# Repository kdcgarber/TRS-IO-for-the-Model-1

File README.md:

# TRS-IO model 1

This repo is based on a snapshot of https://github.com/apuder/TRS-IO commit f2acde6.<br>
That repo is an amazing piece of hardware/software that provides new feature to my retro TRS-80 model 1<br>

<table>
  <tr>
    <td>
      <ul>
        <li>Network connection / internet - TCP</li>
        <li>Retrostore</li>
        <li>SMB share</li>
        <li>SD card</li>
        <li>FreHD emulation auto-boot on my unmodified M1</li>
        <li>Upper 32k of memory</li>
        <li>Virtual printer</li>
        <li>HDMI color video / audio out</li>
        <li>Realtime clock</li>
      </ul>
    </td>
    <td>
      
    </td>
  </tr>
</table>

These are just notes for my path to get the v1.4 hardware build configured with the backported TRS-IO++ software that is all found on their site.<br>
Their site is the safe source and is what should be used; mine is just my notes and everything that worked for me.
These are my notes to help me build another in the future and could possibly help someone else as well.<br>
<br>

These are not notes on the pcb build, just the code deploy process for the TRS-IO v1.4.<br>

## Notes

I used the ESP-WROOM-32 esp controller (no PSRAM) - https://www.amazon.com/dp/B0B764963C<br>
And I used the Tang Nano 9K FPGA - https://www.aliexpress.us/item/3256804089255675.html<br>

I did this install/build/deploy on my OrangePi-Zero-2w running Ubuntu 24.04, as a non-root account<br>

### Prep - installing required components<br>
&nbsp;&nbsp;&nbsp;&nbsp;sudo apt upgrade<br>
### Packages for Espressif<br>
&nbsp;&nbsp;&nbsp;&nbsp;sudo apt-get install git wget flex bison gperf python3 python3-pip python3-setuptools cmake ninja-build ccache libffi-dev libssl-dev dfu-util libusb-1.0-0 python3-virtualenv<br>
###  Packages for TRS-IO<br>
&nbsp;&nbsp;&nbsp;&nbsp;sudo apt-get install z80asm sdcc sdcc-libraries<br>
###  Some fixes for linking libraries that are needed by TRS-IO<br>
&nbsp;&nbsp;&nbsp;&nbsp;sudo mkdir -p /lib/z80/<br>
&nbsp;&nbsp;&nbsp;&nbsp;sudo ln -s /usr/share/sdcc/lib/z80/z80.lib /lib/z80/z80.lib<br>
###  Python3 as default:<br>
&nbsp;&nbsp;&nbsp;&nbsp;sudo apt-get install python3 python3-pip python3-setuptools<br>
&nbsp;&nbsp;&nbsp;&nbsp;sudo ln -s /usr/bin/python3 /usr/bin/python<br>
<br>

###  Install ESP-IDF<br>
cd ~/<br>
mkdir esp<br>
cd esp<br>
git clone -b v4.4.7 --recurse-submodules https://github.com/espressif/esp-idf.git<br>
cd ~/esp/esp-idf<br>
./install.sh esp32<br>

### TRS-IO stuff<br>
.  ~/esp/esp-idf/export.sh<br>
cd ~/esp<br>
git clone -b master --recurse-submodules https://github.com/apuder/TRS-IO.git <br>
cd ~/esp/TRS-IO/src/esp/ <br>

### Copy sdkconfig.trs-io-m1 to sdkconfig.trs-io-m1-v14<br>
cp sdkconfig.trs-io-m1 sdkconfig.trs-io-m1-v14<br>
<br>
### Then add to the bottom of the sdkconfig.trs-io-m1-v14<br>
CONFIG_SPIRAM_SUPPORT=n<br>

### Added logging to the event handler   ~/esp/TRS-IO/src/esp/components/trs-io/http.cpp <br>
This is not required, I add additional logging just lets me validate memory available as the event handler is triggered at the time of the showing of web server events.<br>
    ESP_LOGI(TAG, "Free heap: %u", esp_get_free_heap_size());<br>

vim   ~/esp/TRS-IO/src/esp/components/trs-io/http.cpp <br>
It should look like this<br>

	static void mongoose_event_handler(struct mg_connection *c,
					   int event, void *eventData, void *fn_data)
	{
	  static bool reboot = false;

	  // Return if the web debugger is handling the request.
	  if (trx_handle_http_request(c, event, eventData, fn_data)) {
	    return;
	  }

	  switch (event) {
	  case MG_EV_HTTP_MSG:
	    {
	      struct mg_http_message* message = (struct mg_http_message*) eventData;
	      ESP_LOGI(TAG, "request %.*s %.*s",
		      message->method.len,
		      message->method.ptr,
		      message->uri.len,
		      message->uri.ptr);

	      ESP_LOGI(TAG, "Free heap: %u", esp_get_free_heap_size());

	      char* response = NULL; // Always allocated.
	      const char* content_type = "text/html"; // Never allocated

<br>

### Then lowered the max_files value to save memory for the SD card usage.<br>

vim components/trs-fs/posix.cpp<br>
 .max_files = 3,  // 2 works also -- changed from 5<br>

<br>

### Then I changed the LED GPIO values to match the colors for the current v1.4 PCB since mine are RGB, not RBG<br>

This is not needed if you buy LEDs that are RBG, instead of what I bought.<vr>
vim ~/esp/TRS-IO/src/esp/main/led.cpp<br>
#ifdef CONFIG_TRS_IO_MODEL_1<br>
#define LED_RED 5<br>
#define LED_GREEN 4<br>
#define LED_BLUE 32<br>
<br>

# Build<br>
cd ~/esp/TRS-IO/src/esp<br>
idf.py fullclean<br>
make BOARD=trs-io-m1-v14 build<br>

The build will show many  warnings, but if it completes with no errors, the the rest should be good.<br>
At the bottom of its output, it lists the command to run. The port needs to be changed to match the correct port.<br>

Sometimes while doing the flash, it fails. If it does, just try it again and it will load.<br><br>
~/esp/esp-idf/components/esptool_py/esptool/esptool.py -p /dev/ttyUSB0  -b 460800 --before default_reset --after hard_reset --chip esp32  write_flash --flash_mode dio --flash_size detect --flash_freq 40m 0x1000 build/bootloader/bootloader.bin 0x8000 build/partition_table/partition-table.bin 0x10000 build/trs-io.bin 0x190000 build/html.bin<br>

<br><br><br>

# Flash the FPGA

### Install openFPGALoader

apt install \\<br>
  git \\<br>
  gzip \\<br>
  libftdi1-2 \\<br>
  libftdi1-dev \\<br>
  libhidapi-hidraw0 \\<br>
  libhidapi-dev \\<br>
  libudev-dev \\<br>
  zlib1g-dev \\<br>
  cmake \\<br>
  pkg-config \\<br>
  make \\<br>
  g++

git clone https://github.com/trabucayre/openFPGALoader<br>
cd openFPGALoader<br>
mkdir build<br>
cd build<br>
cmake .. <br>
cmake --build .<br>
make install<br>

### The FPGA file is TRS-IO.fs<br>

cd  ~/esp/build<br>
openFPGALoader -b tangnano9k -f TRS-IO.fs

		EXAMPLE:
		root@thebox:/home/kdcgarber/esp/buildFiles# openFPGALoader -b tangnano9k -f TRS-IO.fs
		
		empty
		write to flash
		Jtag frequency : requested 6.00MHz   -> real 6.00MHz
		Parse file Parse TRS-IO.fs:
		Done
		DONE
		Jtag frequency : requested 2.50MHz   -> real 2.00MHz
		Erase SRAM DONE
		Erase FLASH DONE
		Erasing FLASH: [==================================================] 100.00%
		Done
		write Flash: [==================================================] 100.00%
		Done
		CRC check: Success

<br>

## All done with the Install

After the install is complete, follow the notes on the TRS-IO site to bring up the trs-io.local access point and start the configuration.<br>
The site has the ROM boot loader for the FreHD to go on the SD card or the smb (windows share or for me SAMBA share on my Linux server).<br>

<br><br><br><br>

## Other notes

### FPGA LED values
wire esp_status_esp_ready   = esp_status[0];<br>
wire esp_status_wifi_up     = esp_status[1];<br>
wire esp_status_smb_mounted = esp_status[2];<br>
wire esp_status_sd_mounted  = esp_status[3];<br>

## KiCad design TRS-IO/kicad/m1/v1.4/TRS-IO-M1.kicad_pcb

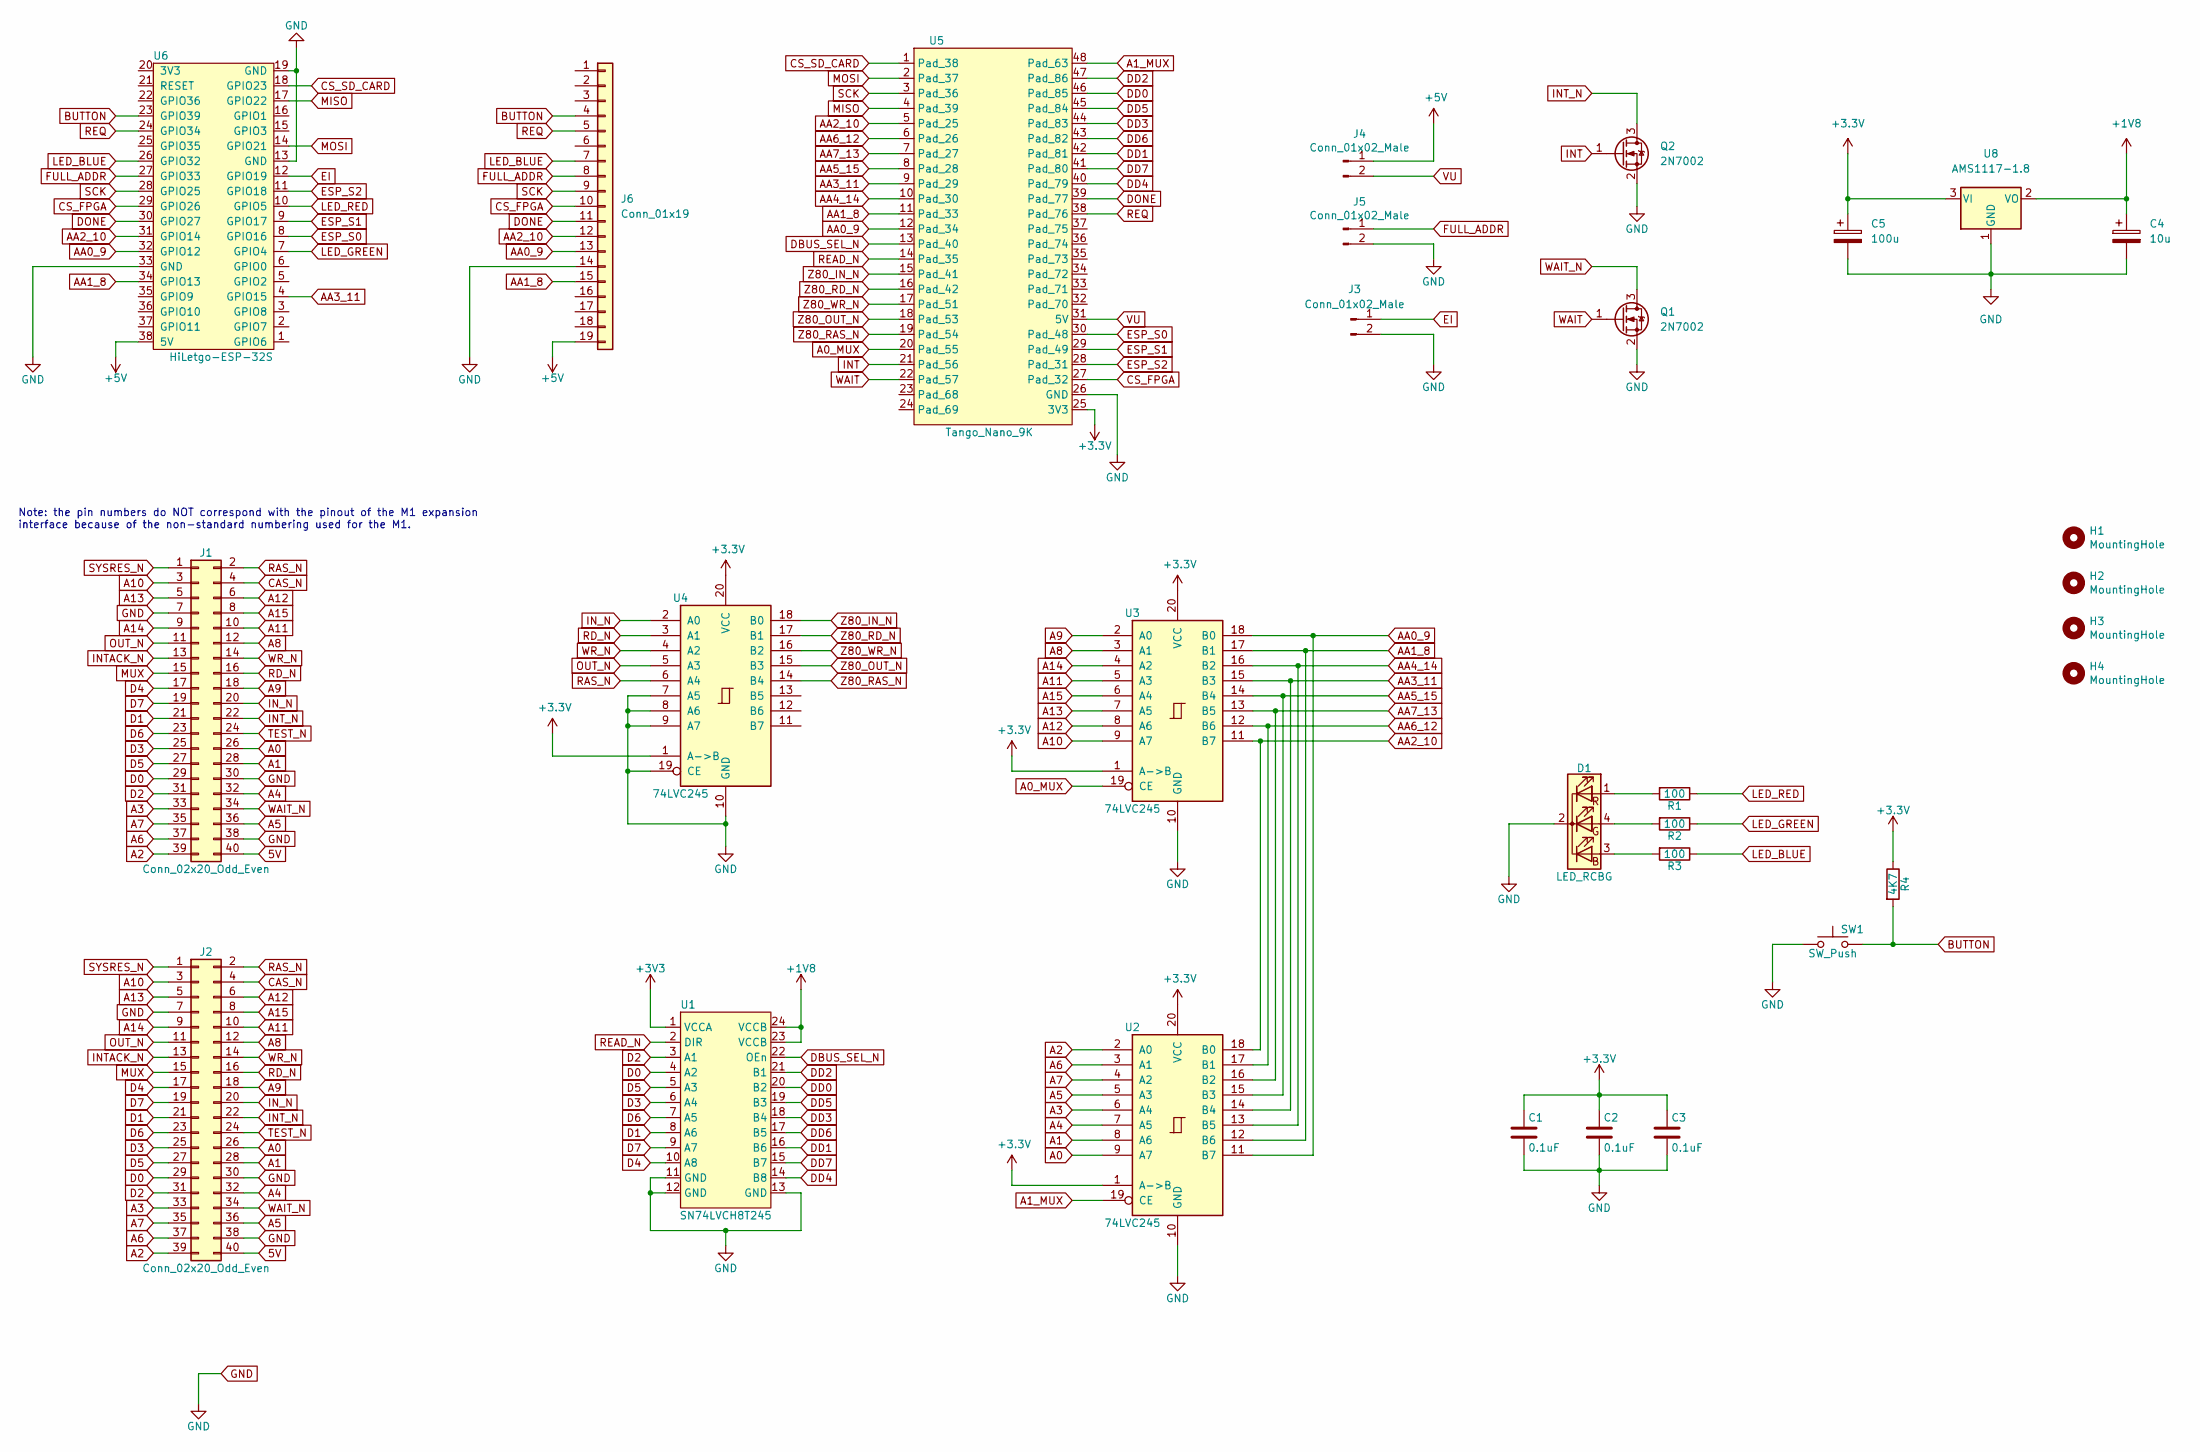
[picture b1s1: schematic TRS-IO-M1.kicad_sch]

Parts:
C1, C2, C3: 0.1uF; C_0805_2012Metric_Pad1.18x1.45mm_HandSolder
C4: 10u; C_1206_3216Metric_Pad1.33x1.80mm_HandSolder
C5: 100u; C_1206_3216Metric_Pad1.33x1.80mm_HandSolder
D1: LED_RCBG; LED_D5.0mm-4_RGB
H1, H2, H3, H4: MountingHole; MountingHole_3mm_Pad_Via
J1: Conn_02x20_Odd_Even; PinHeader_2x20_P2.54mm_Vertical
J2: Conn_02x20_Odd_Even; TRSEDGE
J3, J4, J5: Conn_01x02_Male; PinHeader_1x02_P2.54mm_Vertical
J6: Conn_01x19; PinHeader_1x19_P2.54mm_Vertical
Q1, Q2: 2N7002; SOT-23
R1, R2, R3: 100; R_0805_2012Metric_Pad1.20x1.40mm_HandSolder
R4: 4K7; R_0805_2012Metric_Pad1.20x1.40mm_HandSolder
SW1: SW_Push; SW_PUSH_6mm_H9.5mm
U1: SN74LVCH8T245; TSSOP-24_4.4x7.8mm_P0.65mm
U2, U3, U4: 74LVC245; SSOP-20_5.3x7.2mm_P0.65mm_slim
U5: Tango_Nano_9K; DIP-48_W22.9mm
U6: HiLetgo-ESP-32S; DIP-38_W22.9mm
U8: AMS1117-1.8; SOT-223-3_TabPin2

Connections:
5V: J1.40, J2.40
+1V8: C4.1, U1.23 (VCCB), U1.24 (VCCB), U8.2 (VO)
+5V: J4.1, J6.19, U6.38 (5V)
A0: J1.26, J2.26, U2.9 (A7)
A0_MUX: U3.19 (CE), U5.20 (Pad_55)
A1: J1.28, J2.28, U2.8 (A6)
A1_MUX: U2.19 (CE), U5.48 (Pad_63)
A2: J1.39, J2.39, U2.2 (A0)
A3: J1.33, J2.33, U2.6 (A4)
A4: J1.32, J2.32, U2.7 (A5)
A5: J1.36, J2.36, U2.5 (A3)
A6: J1.37, J2.37, U2.3 (A1)
A7: J1.35, J2.35, U2.4 (A2)
A8: J1.12, J2.12, U3.3 (A1)
A9: J1.18, J2.18, U3.2 (A0)
A10: J1.3, J2.3, U3.9 (A7)
A11: J1.10, J2.10, U3.5 (A3)
A12: J1.6, J2.6, U3.8 (A6)
A13: J1.5, J2.5, U3.7 (A5)
A14: J1.9, J2.9, U3.4 (A2)
A15: J1.8, J2.8, U3.6 (A4)
AA0_9: J6.13, U2.11 (B7), U3.18 (B0), U5.12 (Pad_34), U6.32 (GPIO12)
AA1_8: J6.15, U2.12 (B6), U3.17 (B1), U5.11 (Pad_33), U6.34 (GPIO13)
AA2_10: J6.12, U2.18 (B0), U3.11 (B7), U5.5 (Pad_25), U6.31 (GPIO14)
AA3_11: U2.14 (B4), U3.15 (B3), U5.9 (Pad_29), U6.4 (GPIO15)
AA4_14: U2.13 (B5), U3.16 (B2), U5.10 (Pad_30)
AA5_15: U2.15 (B3), U3.14 (B4), U5.8 (Pad_28)
AA6_12: U2.17 (B1), U3.12 (B6), U5.6 (Pad_26)
AA7_13: U2.16 (B2), U3.13 (B5), U5.7 (Pad_27)
BUTTON: J6.4, R4.2, SW1.2, U6.23 (GPIO39)
CAS_N: J1.4, J2.4
CS_FPGA: J6.10, U5.27 (Pad_32), U6.29 (GPIO26)
CS_SD_CARD: U5.1 (Pad_38), U6.18 (GPIO23)
D0: J1.29, J2.29, U1.4 (A2)
D1: J1.21, J2.21, U1.8 (A6)
D2: J1.31, J2.31, U1.3 (A1)
D3: J1.25, J2.25, U1.6 (A4)
D4: J1.17, J2.17, U1.10 (A8)
D5: J1.27, J2.27, U1.5 (A3)
D6: J1.23, J2.23, U1.7 (A5)
D7: J1.19, J2.19, U1.9 (A7)
DBUS_SEL_N: U1.22 (OEn), U5.13 (Pad_40)
DD0: U1.20 (B2), U5.46 (Pad_85)
DD1: U1.16 (B6), U5.42 (Pad_81)
DD2: U1.21 (B1), U5.47 (Pad_86)
DD3: U1.18 (B4), U5.44 (Pad_83)
DD4: U1.14 (B8), U5.40 (Pad_79)
DD5: U1.19 (B3), U5.45 (Pad_84)
DD6: U1.17 (B5), U5.43 (Pad_82)
DD7: U1.15 (B7), U5.41 (Pad_80)
DONE: J6.11, U5.39 (Pad_77), U6.30 (GPIO27)
EI: J3.1, U6.12 (GPIO19)
ESP_S0: U5.30 (Pad_48), U6.8 (GPIO16)
ESP_S1: U5.29 (Pad_49), U6.9 (GPIO17)
ESP_S2: U5.28 (Pad_31), U6.11 (GPIO18)
FULL_ADDR: J5.1, J6.8, U6.27 (GPIO33)
GND: C1.2, C2.2, C3.2, C4.2, C5.2, D1.2 (K), J1.7, J1.30, J1.38, J2.7, J2.30, J2.38, J3.2, J5.2, J6.14, Q1.2 (S), Q2.2 (S), SW1.1, U1.11 (GND), U1.12 (GND), U1.13 (GND), U2.10 (GND), U3.10 (GND), U4.7 (A5), U4.8 (A6), U4.9 (A7), U4.10 (GND), U4.19 (CE), U5.26 (GND), U6.13 (GND), U6.19 (GND), U6.33 (GND), U8.1 (GND)
INT: Q2.1 (G), U5.21 (Pad_56)
INTACK_N: J1.13, J2.13
INT_N: J1.22, J2.22, Q2.3 (D)
IN_N: J1.20, J2.20, U4.2 (A0)
LED_BLUE: J6.7, R3.1, U6.26 (GPIO32)
LED_GREEN: R2.1, U6.7 (GPIO4)
LED_RED: R1.1, U6.10 (GPIO5)
MISO: U5.4 (Pad_39), U6.17 (GPIO22)
MOSI: U5.2 (Pad_37), U6.14 (GPIO21)
MUX: J1.15, J2.15
unnamed: D1.1 (RA), R1.2
unnamed: D1.3 (BA), R3.2
unnamed: D1.4 (GA), R2.2
OUT_N: J1.11, J2.11, U4.5 (A3)
RAS_N: J1.2, J2.2, U4.6 (A4)
RD_N: J1.16, J2.16, U4.3 (A1)
READ_N: U1.2 (DIR), U5.14 (Pad_35)
REQ: J6.5, U5.38 (Pad_76), U6.24 (GPIO34)
SCK: J6.9, U5.3 (Pad_36), U6.28 (GPIO25)
SYSRES_N: J1.1, J2.1
TEST_N: J1.24, J2.24
VU: J4.2, U5.31 (5V)
WAIT: Q1.1 (G), U5.22 (Pad_57)
WAIT_N: J1.34, J2.34, Q1.3 (D)
WR_N: J1.14, J2.14, U4.4 (A2)
Z80_IN_N: U4.18 (B0), U5.15 (Pad_41)
Z80_OUT_N: U4.15 (B3), U5.18 (Pad_53)
Z80_RAS_N: U4.14 (B4), U5.19 (Pad_54)
Z80_RD_N: U4.17 (B1), U5.16 (Pad_42)
Z80_WR_N: U4.16 (B2), U5.17 (Pad_51)

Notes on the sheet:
Note: the pin numbers do NOT correspond with the pinout of the M1 expansion interface because of the non-standard numbering used for the M1.

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
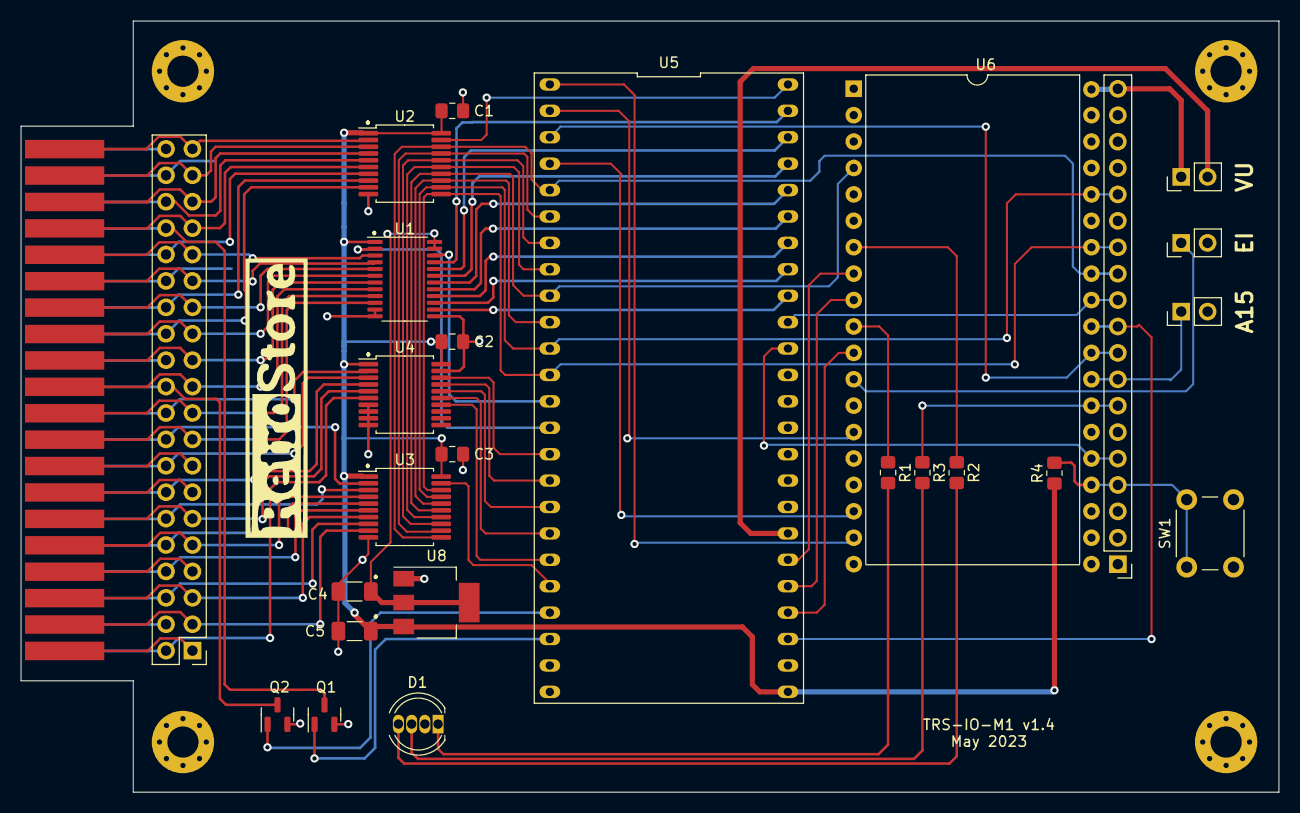
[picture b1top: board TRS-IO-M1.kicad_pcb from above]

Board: 2 copper layers, 121.0 x 74.2 mm, 31 parts (0 on the bottom side), 88 nets.

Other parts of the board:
G1: LOGO

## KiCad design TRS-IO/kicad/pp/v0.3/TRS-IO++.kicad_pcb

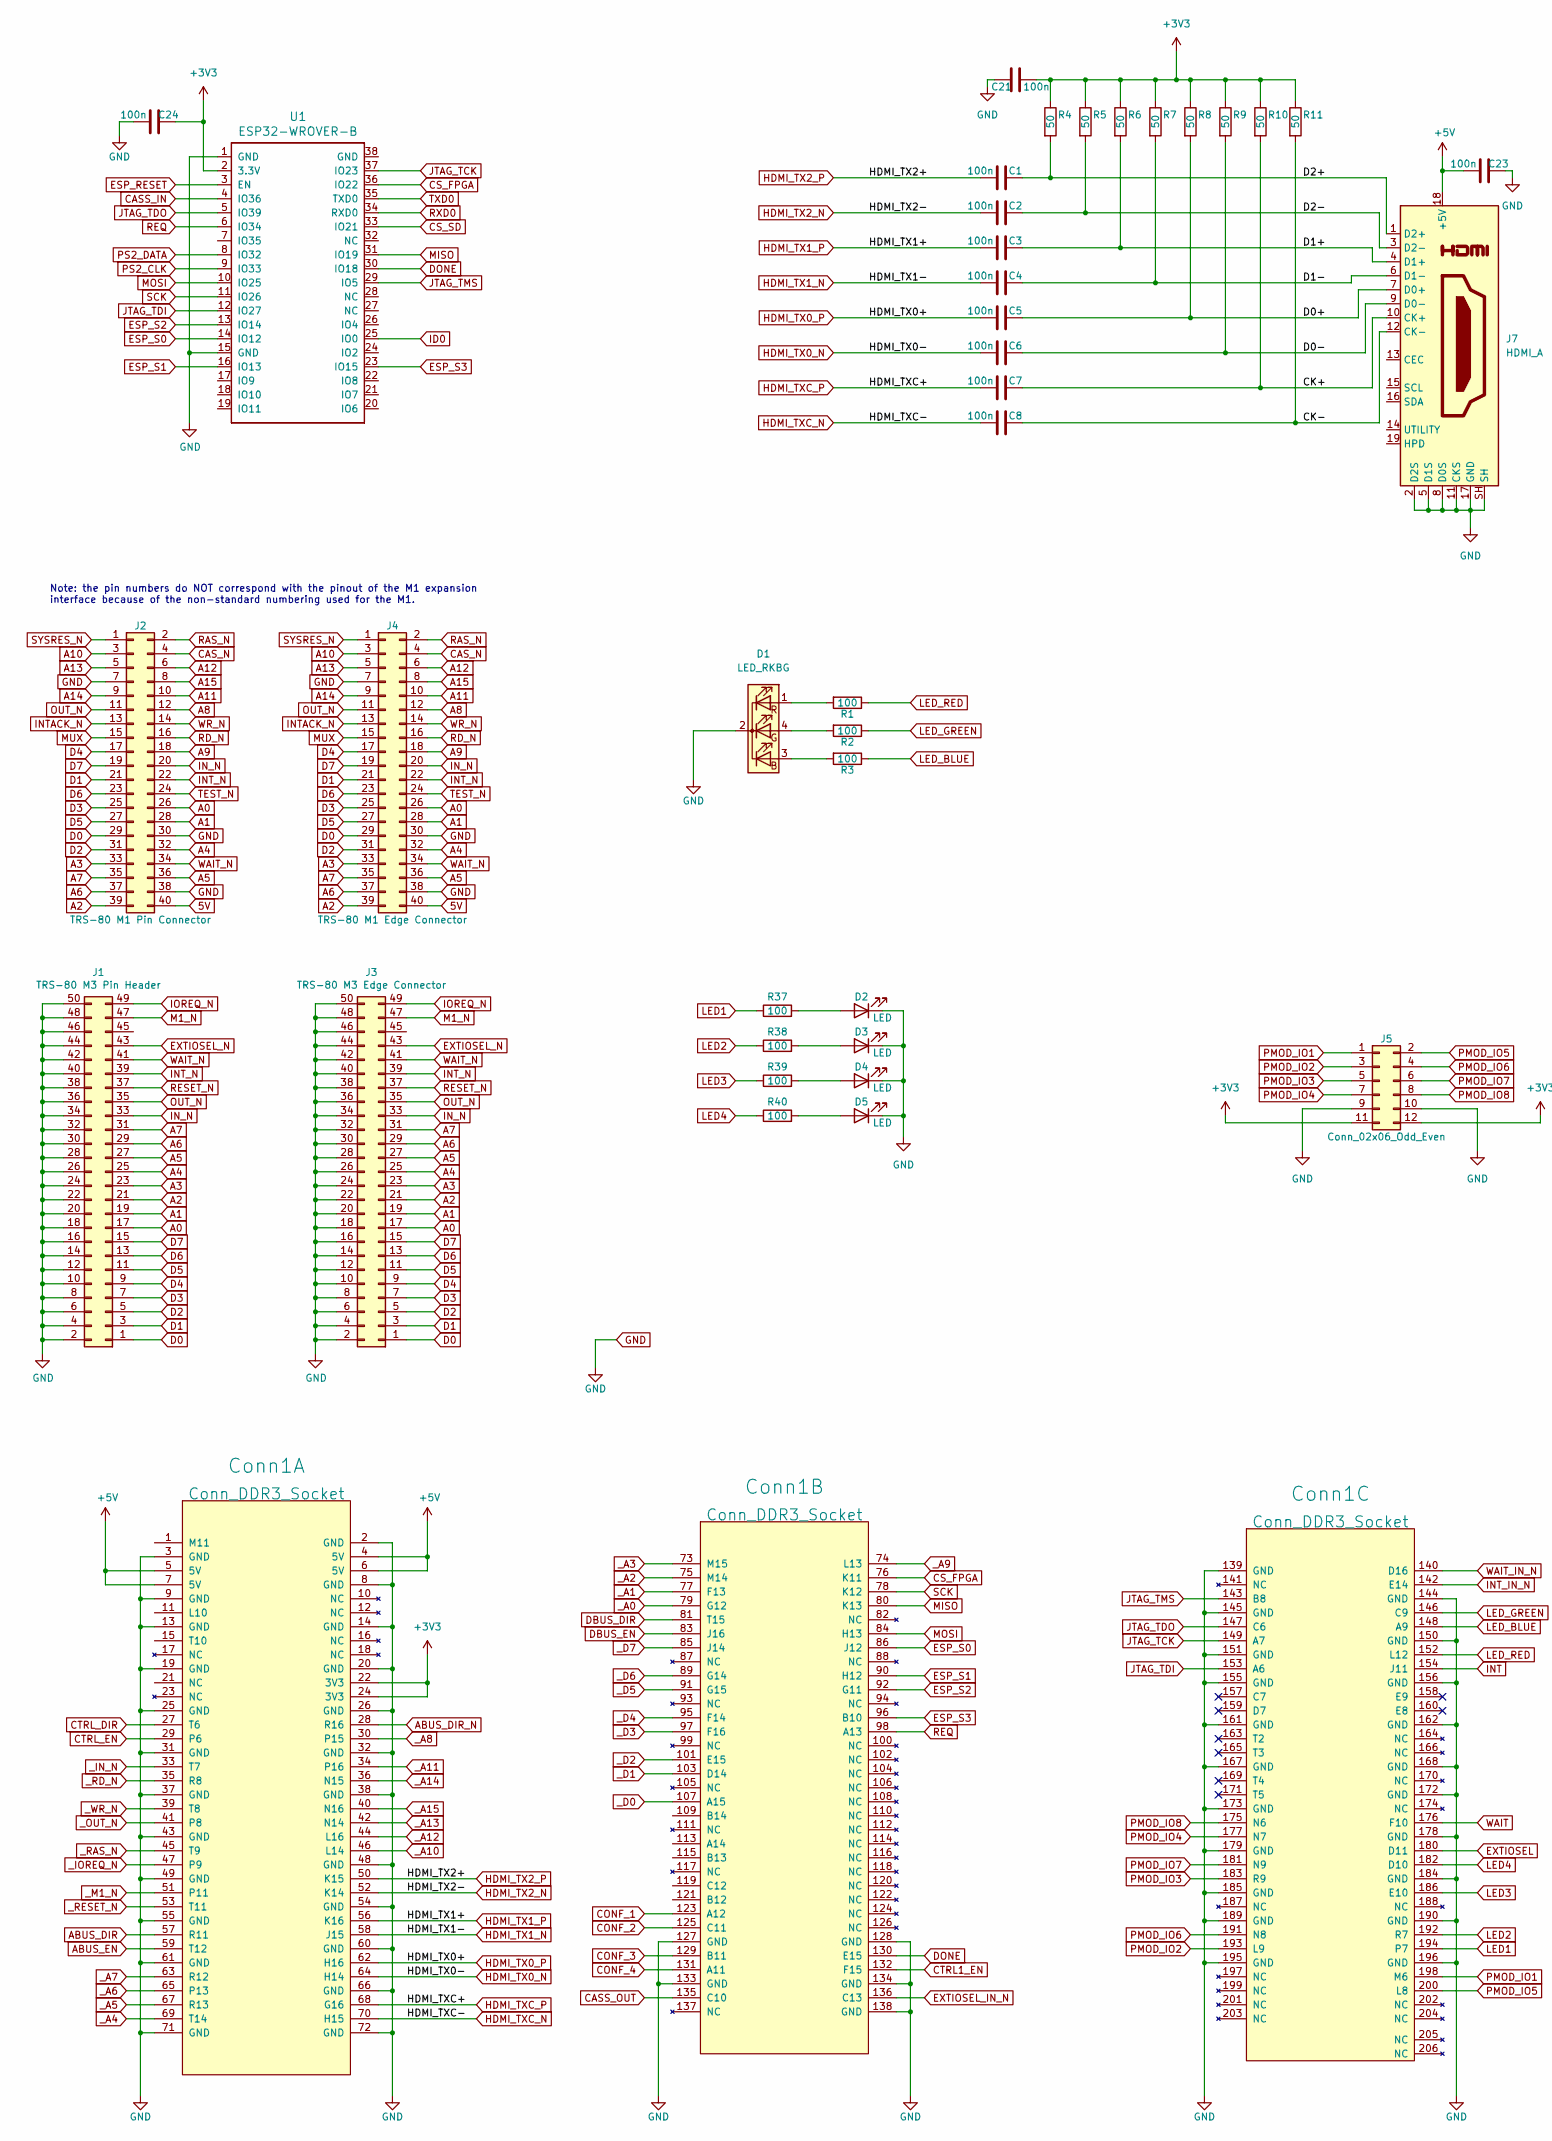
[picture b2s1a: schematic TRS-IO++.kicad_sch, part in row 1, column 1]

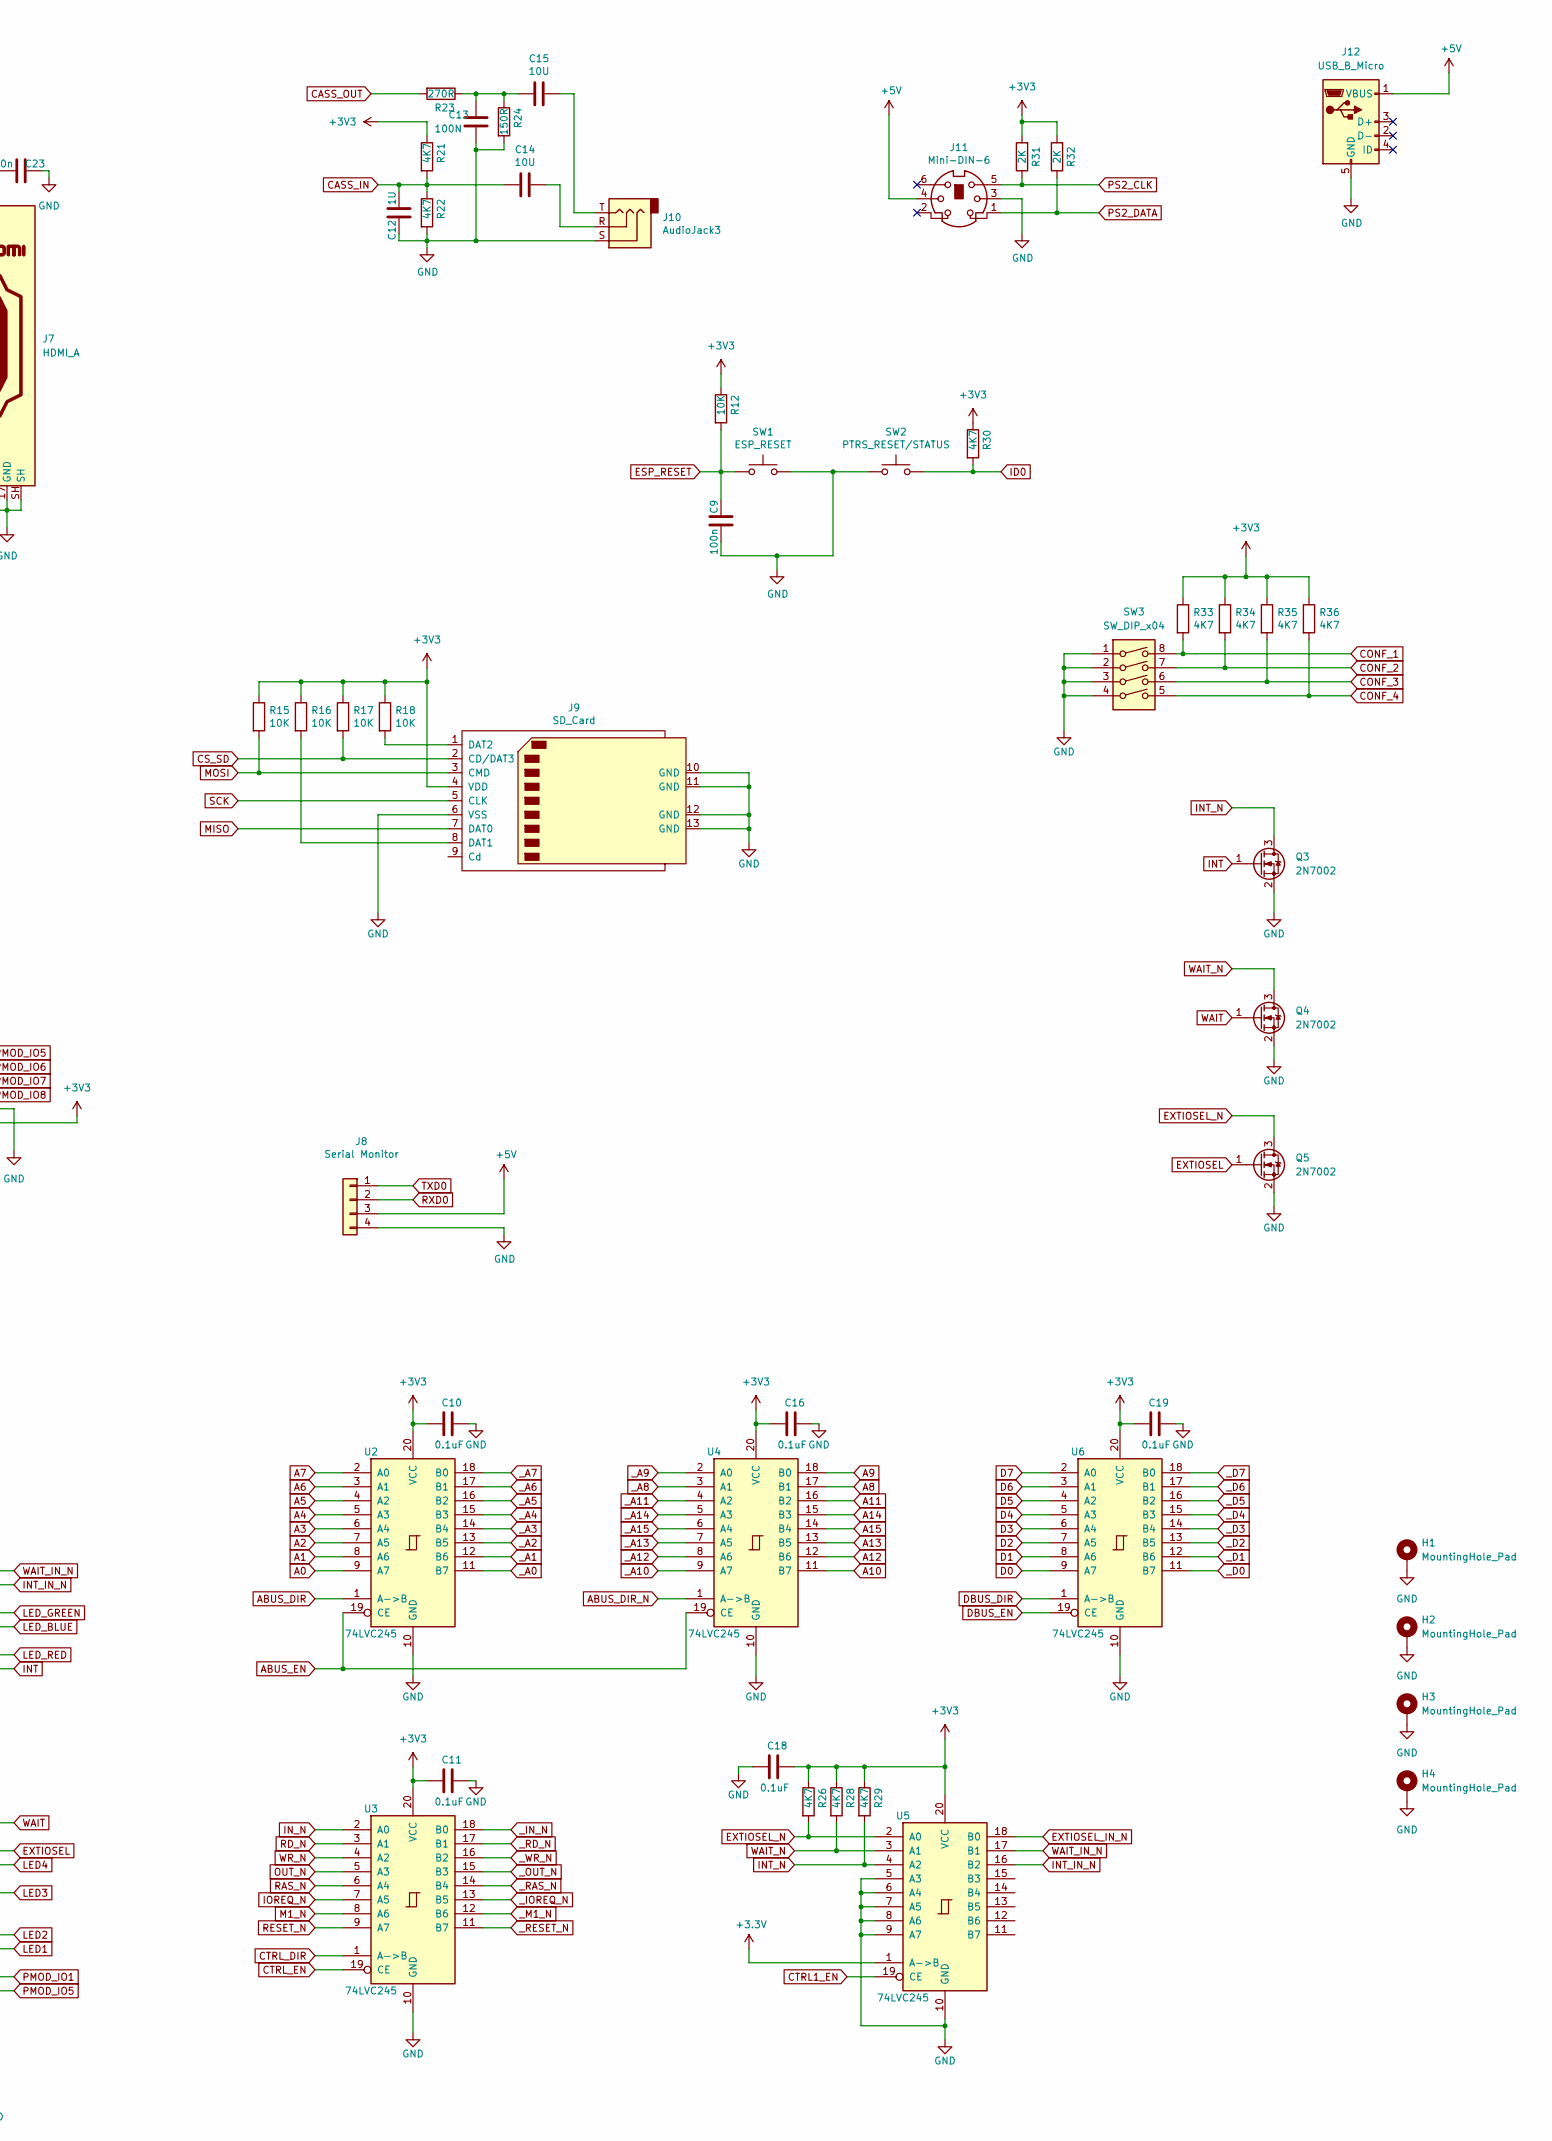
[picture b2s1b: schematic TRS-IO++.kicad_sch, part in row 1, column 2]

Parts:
C1, C2, C3, C4, C5, C6, C7, C8, C9, C21, C23, C24: 100n; C_0805_2012Metric_Pad1.18x1.45mm_HandSolder
C10, C11, C16, C18, C19: 0.1uF; C_0805_2012Metric_Pad1.18x1.45mm_HandSolder
C12: 1U; C_1206_3216Metric_Pad1.33x1.80mm_HandSolder
C13: 100N; C_0805_2012Metric_Pad1.18x1.45mm_HandSolder
C14, C15: 10U; C_1206_3216Metric_Pad1.33x1.80mm_HandSolder
Conn1: Conn_DDR3_Socket; DDR3_socket
D1: LED_RKBG; LED_D5.0mm-4_RGB
D2, D3, D4, D5: LED; LED_0805_2012Metric_Pad1.15x1.40mm_HandSolder
H1, H2, H3, H4: MountingHole_Pad; MountingHole_3mm_Pad_Via
J1: TRS-80 M3 Pin Header; PinHeader_2x25_P2.54mm_Vertical
J2: TRS-80 M1 Pin Connector; PinHeader_2x20_P2.54mm_Vertical
J3: TRS-80 M3 Edge Connector; EDGE50
J4: TRS-80 M1 Edge Connector; TRSEDGE
J5: Conn_02x06_Odd_Even; PinSocket_2x06_P2.54mm_Vertical
J7: HDMI_A; HDMI_A_Molex_208658-1001_Horizontal
J8: Serial Monitor; PinSocket_1x04_P2.54mm_Vertical
J9: SD_Card; TFP09-2-12B
J10: AudioJack3; Jack_3.5mm_CUI_SJ1-3535NG_Horizontal_CircularHoles
J11: Mini-DIN-6; minidin_6_ps2_pcb_mount
J12: USB_B_Micro; USBmicro-B
Q3, Q4, Q5: 2N7002; SOT-23
R1, R2, R3, R37, R38, R39, R40: 100; R_0805_2012Metric_Pad1.20x1.40mm_HandSolder
R4, R5, R6, R7, R8, R9, R10, R11: 50; R_0805_2012Metric_Pad1.20x1.40mm_HandSolder
R12, R15, R16, R17, R18: 10K; R_0805_2012Metric_Pad1.20x1.40mm_HandSolder
R21, R22, R26, R28, R29, R30, R33, R34, R35, R36: 4K7; R_0805_2012Metric_Pad1.20x1.40mm_HandSolder
R23: 270R; R_0805_2012Metric_Pad1.20x1.40mm_HandSolder
R24: 150R; R_0805_2012Metric_Pad1.20x1.40mm_HandSolder
R31, R32: 2K; R_0805_2012Metric_Pad1.20x1.40mm_HandSolder
SW1: ESP_RESET; SW_PUSH_6mm
SW2: PTRS_RESET/STATUS; SW_PUSH_6mm
SW3: SW_DIP_x04; SW_DIP_SPSTx04_Slide_6.7x11.72mm_W8.61mm_P2.54mm_LowProfile
U1: ESP32-WROVER-B; ESP32-WROVER
U2, U3, U4, U5, U6: 74LVC245; SSOP-20_5.3x7.2mm_P0.65mm_slim

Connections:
5V: J2.40, J4.40
+5V: C23.1, Conn1.4 (5V), Conn1.5 (5V), Conn1.6 (5V), Conn1.7 (5V), J7.18 (+5V), J8.3, J11.4, J12.1 (VBUS)
/CK+: C7.2, J7.10 (CK+), R10.2
/CK-: C8.2, J7.12 (CK-), R11.2
/D0+: C5.2, J7.7 (D0+), R8.2
/D0-: C6.2, J7.9 (D0-), R9.2
/D1+: C3.2, J7.4 (D1+), R6.2
/D1-: C4.2, J7.6 (D1-), R7.2
/D2+: C1.2, J7.1 (D2+), R4.2
/D2-: C2.2, J7.3 (D2-), R5.2
A0: J1.17, J2.26, J3.17, J4.26, U2.9 (A7)
A1: J1.19, J2.28, J3.19, J4.28, U2.8 (A6)
A2: J1.21, J2.39, J3.21, J4.39, U2.7 (A5)
A3: J1.23, J2.33, J3.23, J4.33, U2.6 (A4)
A4: J1.25, J2.32, J3.25, J4.32, U2.5 (A3)
A5: J1.27, J2.36, J3.27, J4.36, U2.4 (A2)
A6: J1.29, J2.37, J3.29, J4.37, U2.3 (A1)
A7: J1.31, J2.35, J3.31, J4.35, U2.2 (A0)
A8: J2.12, J4.12, U4.17 (B1)
A9: J2.18, J4.18, U4.18 (B0)
A10: J2.3, J4.3, U4.11 (B7)
A11: J2.10, J4.10, U4.16 (B2)
A12: J2.6, J4.6, U4.12 (B6)
A13: J2.5, J4.5, U4.13 (B5)
A14: J2.9, J4.9, U4.15 (B3)
A15: J2.8, J4.8, U4.14 (B4)
ABUS_DIR: Conn1.57 (R11), U2.1 (A->B)
ABUS_DIR_N: Conn1.28 (R16), U4.1 (A->B)
ABUS_EN: Conn1.59 (T12), U2.19 (CE), U4.19 (CE)
CASS_IN: C12.1, C14.2, R21.2, R22.1, U1.4 (IO36)
CASS_OUT: Conn1.135 (C10), R23.2
CAS_N: J2.4, J4.4
CONF_1: Conn1.123 (A12), R33.2, SW3.8
CONF_2: Conn1.125 (C11), R34.2, SW3.7
CONF_3: Conn1.129 (B11), R35.2, SW3.6
CONF_4: Conn1.131 (A11), R36.2, SW3.5
CS_FPGA: Conn1.76 (K11), U1.36 (IO22)
CS_SD: J9.2 (CD/DAT3), R17.2, U1.33 (IO21)
CTRL1_EN: Conn1.132 (F15), U5.19 (CE)
CTRL_DIR: Conn1.27 (T6), U3.1 (A->B)
CTRL_EN: Conn1.29 (P6), U3.19 (CE)
D0: J1.1, J2.29, J3.1, J4.29, U6.9 (A7)
D1: J1.3, J2.21, J3.3, J4.21, U6.8 (A6)
D2: J1.5, J2.31, J3.5, J4.31, U6.7 (A5)
D3: J1.7, J2.25, J3.7, J4.25, U6.6 (A4)
D4: J1.9, J2.17, J3.9, J4.17, U6.5 (A3)
D5: J1.11, J2.27, J3.11, J4.27, U6.4 (A2)
D6: J1.13, J2.23, J3.13, J4.23, U6.3 (A1)
D7: J1.15, J2.19, J3.15, J4.19, U6.2 (A0)
DBUS_DIR: Conn1.81 (T15), U6.1 (A->B)
DBUS_EN: Conn1.83 (J16), U6.19 (CE)
DONE: Conn1.130 (E15), U1.30 (IO18)
ESP_RESET: C9.2, R12.2, SW1.1, U1.3 (EN)
ESP_S0: Conn1.86 (J12), U1.14 (IO12)
ESP_S1: Conn1.90 (H12), U1.16 (IO13)
ESP_S2: Conn1.92 (G11), U1.13 (IO14)
ESP_S3: Conn1.96 (B10), U1.23 (IO15)
EXTIOSEL: Conn1.180 (D11), Q5.1 (G)
EXTIOSEL_IN_N: Conn1.136 (C13), U5.18 (B0)
EXTIOSEL_N: J1.43, J3.43, Q5.3 (D), R26.2, U5.2 (A0)
GND: C9.1, C10.1, C11.1, C12.2, C13.2, C16.1, C18.2, C19.1, C21.2, C23.2, C24.1, Conn1.2 (GND), Conn1.3 (GND), Conn1.8 (GND), Conn1.9 (GND), Conn1.13 (GND), Conn1.14 (GND), Conn1.19 (GND), Conn1.20 (GND), Conn1.25 (GND), Conn1.26 (GND), Conn1.31 (GND), Conn1.32 (GND), Conn1.37 (GND), Conn1.38 (GND), Conn1.43 (GND), Conn1.48 (GND), Conn1.49 (GND), Conn1.54 (GND), Conn1.55 (GND), Conn1.60 (GND), Conn1.61 (GND), Conn1.66 (GND), Conn1.71 (GND), Conn1.72 (GND), Conn1.127 (GND), Conn1.128 (GND), Conn1.133 (GND), Conn1.134 (GND), Conn1.138 (GND), Conn1.139 (GND), Conn1.144 (GND), Conn1.145 (GND), Conn1.150 (GND), Conn1.151 (GND), Conn1.155 (GND), Conn1.156 (GND), Conn1.161 (GND), Conn1.162 (GND), Conn1.167 (GND), Conn1.168 (GND), Conn1.172 (GND), Conn1.173 (GND), Conn1.178 (GND), Conn1.179 (GND), Conn1.184 (GND), Conn1.185 (GND), Conn1.189 (GND), Conn1.190 (GND), Conn1.195 (GND), Conn1.196 (GND), D1.2 (K), D2.1 (K), D3.1 (K), D4.1 (K), D5.1 (K), H1.1, H2.1, H3.1, H4.1, J1.2, J1.4, J1.6, J1.8, J1.10, J1.12, J1.14, J1.16, J1.18, J1.20, J1.22, J1.24, J1.26, J1.28, J1.30, J1.32, J1.34, J1.36, J1.38, J1.40, J1.42, J1.44, J1.46, J1.48, J1.50, J2.7, J2.30, J2.38, J3.2, J3.4, J3.6, J3.8, J3.10, J3.12, J3.14, J3.16, J3.18, J3.20, J3.22, J3.24, J3.26, J3.28, J3.30, J3.32, J3.34, J3.36, J3.38, J3.40, J3.42, J3.44, J3.46, J3.48, J3.50, J4.7, J4.30, J4.38, J5.9, J5.10, J7.2 (D2S), J7.5 (D1S), J7.8 (D0S), J7.11 (CKS), J7.17 (GND), J7.SH, J8.4, J9.6 (VSS), J9.10 (GND), J9.11 (GND), J9.12 (GND), J9.13 (GND), J10.S, J11.3, J12.5 (GND), Q3.2 (S), Q4.2 (S), Q5.2 (S), R22.2, R24.2, SW1.2, SW2.1, SW3.1, SW3.2, SW3.3, SW3.4, U1.1 (GND), U1.15 (GND), U2.10 (GND), U3.10 (GND), U4.10 (GND), U5.5 (A3), U5.6 (A4), U5.7 (A5), U5.8 (A6), U5.9 (A7), U5.10 (GND), U6.10 (GND)
HDMI_TX0_N: C6.1, Conn1.64 (H14)
HDMI_TX0_P: C5.1, Conn1.62 (H16)
HDMI_TX1_N: C4.1, Conn1.58 (J15)
HDMI_TX1_P: C3.1, Conn1.56 (K16)
HDMI_TX2_N: C2.1, Conn1.52 (K14)
HDMI_TX2_P: C1.1, Conn1.50 (K15)
HDMI_TXC_N: C8.1, Conn1.70 (H15)
HDMI_TXC_P: C7.1, Conn1.68 (G16)
ID0: R30.2, SW2.2, U1.25 (IO0)
INT: Conn1.154 (J11), Q3.1 (G)
INTACK_N: J2.13, J4.13
INT_IN_N: Conn1.142 (E14), U5.16 (B2)
INT_N: J1.39, J2.22, J3.39, J4.22, Q3.3 (D), R29.2, U5.4 (A2)
IN_N: J1.33, J2.20, J3.33, J4.20, U3.2 (A0)
IOREQ_N: J1.49, J3.49, U3.7 (A5)
JTAG_TCK: Conn1.149 (A7), U1.37 (IO23)
JTAG_TDI: Conn1.153 (A6), U1.12 (IO27)
JTAG_TDO: Conn1.147 (C6), U1.5 (IO39)
JTAG_TMS: Conn1.143 (B8), U1.29 (IO5)
LED1: Conn1.194 (P7), R37.1
LED2: Conn1.192 (R7), R38.1
LED3: Conn1.186 (E10), R39.1
LED4: Conn1.182 (D10), R40.1
LED_BLUE: Conn1.148 (A9), R3.1
LED_GREEN: Conn1.146 (C9), R2.1
LED_RED: Conn1.152 (L12), R1.1
M1_N: J1.47, J3.47, U3.8 (A6)
MISO: Conn1.80 (K13), J9.7 (DAT0), U1.31 (IO19)
MOSI: Conn1.84 (H13), J9.3 (CMD), R15.2, U1.10 (IO25)
MUX: J2.15, J4.15
unnamed: C13.1, C15.2, R23.1, R24.1
unnamed: C14.1, J10.R
unnamed: C15.1, J10.T
unnamed: D1.1 (RA), R1.2
unnamed: D1.3 (BA), R3.2
unnamed: D1.4 (GA), R2.2
unnamed: D2.2 (A), R37.2
unnamed: D3.2 (A), R38.2
unnamed: D4.2 (A), R39.2
unnamed: D5.2 (A), R40.2
unnamed: J9.1 (DAT2), R18.2
unnamed: J9.8 (DAT1), R16.2
OUT_N: J1.35, J2.11, J3.35, J4.11, U3.5 (A3)
PMOD_IO1: Conn1.198 (M6), J5.1
PMOD_IO2: Conn1.193 (L9), J5.3
PMOD_IO3: Conn1.183 (R9), J5.5
PMOD_IO4: Conn1.177 (N7), J5.7
PMOD_IO5: Conn1.200 (L8), J5.2
PMOD_IO6: Conn1.191 (N8), J5.4
PMOD_IO7: Conn1.181 (N9), J5.6
PMOD_IO8: Conn1.175 (N6), J5.8
PS2_CLK: J11.5, R31.1, U1.9 (IO33)
PS2_DATA: J11.1, R32.1, U1.8 (IO32)
RAS_N: J2.2, J4.2, U3.6 (A4)
RD_N: J2.16, J4.16, U3.3 (A1)
REQ: Conn1.98 (A13), U1.6 (IO34)
RESET_N: J1.37, J3.37, U3.9 (A7)
RXD0: J8.2, U1.34 (RXD0)
SCK: Conn1.78 (K12), J9.5 (CLK), U1.11 (IO26)
SYSRES_N: J2.1, J4.1
TEST_N: J2.24, J4.24
TXD0: J8.1, U1.35 (TXD0)
WAIT: Conn1.176 (F10), Q4.1 (G)
WAIT_IN_N: Conn1.140 (D16), U5.17 (B1)
WAIT_N: J1.41, J2.34, J3.41, J4.34, Q4.3 (D), R28.2, U5.3 (A1)
WR_N: J2.14, J4.14, U3.4 (A2)
_A0: Conn1.79 (G12), U2.11 (B7)
_A1: Conn1.77 (F13), U2.12 (B6)
_A2: Conn1.75 (M14), U2.13 (B5)
_A3: Conn1.73 (M15), U2.14 (B4)
_A4: Conn1.69 (T14), U2.15 (B3)
_A5: Conn1.67 (R13), U2.16 (B2)
_A6: Conn1.65 (P13), U2.17 (B1)
_A7: Conn1.63 (R12), U2.18 (B0)
_A8: Conn1.30 (P15), U4.3 (A1)
_A9: Conn1.74 (L13), U4.2 (A0)
_A10: Conn1.46 (L14), U4.9 (A7)
_A11: Conn1.34 (P16), U4.4 (A2)
_A12: Conn1.44 (L16), U4.8 (A6)
_A13: Conn1.42 (N14), U4.7 (A5)
_A14: Conn1.36 (N15), U4.5 (A3)
_A15: Conn1.40 (N16), U4.6 (A4)
_D0: Conn1.107 (A15), U6.11 (B7)
_D1: Conn1.103 (D14), U6.12 (B6)
_D2: Conn1.101 (E15), U6.13 (B5)
_D3: Conn1.97 (F16), U6.14 (B4)
_D4: Conn1.95 (F14), U6.15 (B3)
_D5: Conn1.91 (G15), U6.16 (B2)
_D6: Conn1.89 (G14), U6.17 (B1)
_D7: Conn1.85 (J14), U6.18 (B0)
_IN_N: Conn1.33 (T7), U3.18 (B0)
_IOREQ_N: Conn1.47 (P9), U3.13 (B5)
_M1_N: Conn1.51 (P11), U3.12 (B6)
_OUT_N: Conn1.41 (P8), U3.15 (B3)
_RAS_N: Conn1.45 (T9), U3.14 (B4)
_RD_N: Conn1.35 (R8), U3.17 (B1)
_RESET_N: Conn1.53 (T11), U3.11 (B7)
_WR_N: Conn1.39 (T8), U3.16 (B2)

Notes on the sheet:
Note: the pin numbers do NOT correspond with the pinout of the M1 expansion interface because of the non-standard numbering used for the M1.

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
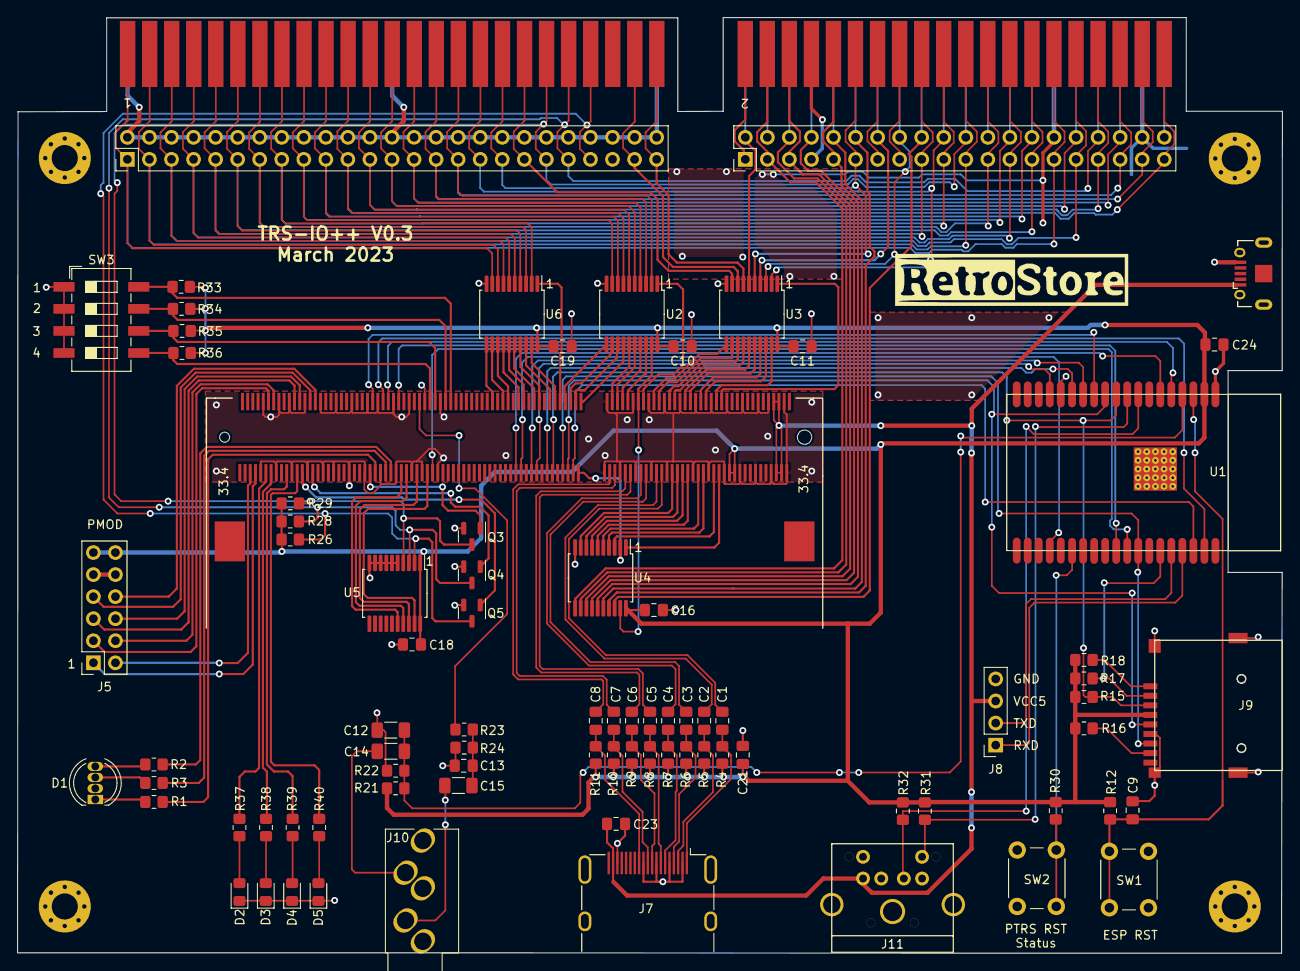
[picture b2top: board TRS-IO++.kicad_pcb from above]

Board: 2 copper layers, 145.7 x 107.8 mm, 89 parts (0 on the bottom side), 160 nets.

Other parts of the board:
G1: LOGO
